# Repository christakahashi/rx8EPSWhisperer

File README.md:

# WARNING
Operating a modified production car can be dangerous or life threatening.  Don't do it.  This project is only for testing your powersteering components in either an otherwise inoperable car or under SLOW SAFE conditions and NEVER on the road or in public. 

# rx8EPSWhisperer
This is a hack to recover the power steering on an RX8 power steering rack thats not longer connected to the ECU.

It reads a potentiometer connected to ADC7 to determine the power steering assist level.

# Hardware
The hardware was designed to be multipurpose as either a CAN sensor interface or to enable the EPS on an RX8.  All components were choosen to be AEC-Q100/AEC-Q200 qualified or have variants that are qualified.  It shoudn't matter for bench test use, but if that matters to you then make sure to buy the right variants.

# Hookup
Connect 12v, ground, CAN+, CAN-, to their respective connections.  If you don't have external termination please close the termination jumper on the PCB.  
To wire it you can either cut the wires on your connector short and run them directly into the PCB making it directly hang off the EPS computer, or you can run longer wires from the 4 pin connector.  Either way 12v and ground need to be connected to the cars accessory power.  

# NOTES
- This isn't a product if anything here doesn't make sense or makes you nervous don't use this hardware/software.
- The can library came modified from atmel, now microchip.  The license referred to in the source for that library can no longer be found, but if its like similar libraries from atmel its free to use as long as its only used on atmel chips.  The licene text file included with this repository only applies to the non-library files.  If you represent atmel/microchip and have clarification or want me to remove the library please contact me.

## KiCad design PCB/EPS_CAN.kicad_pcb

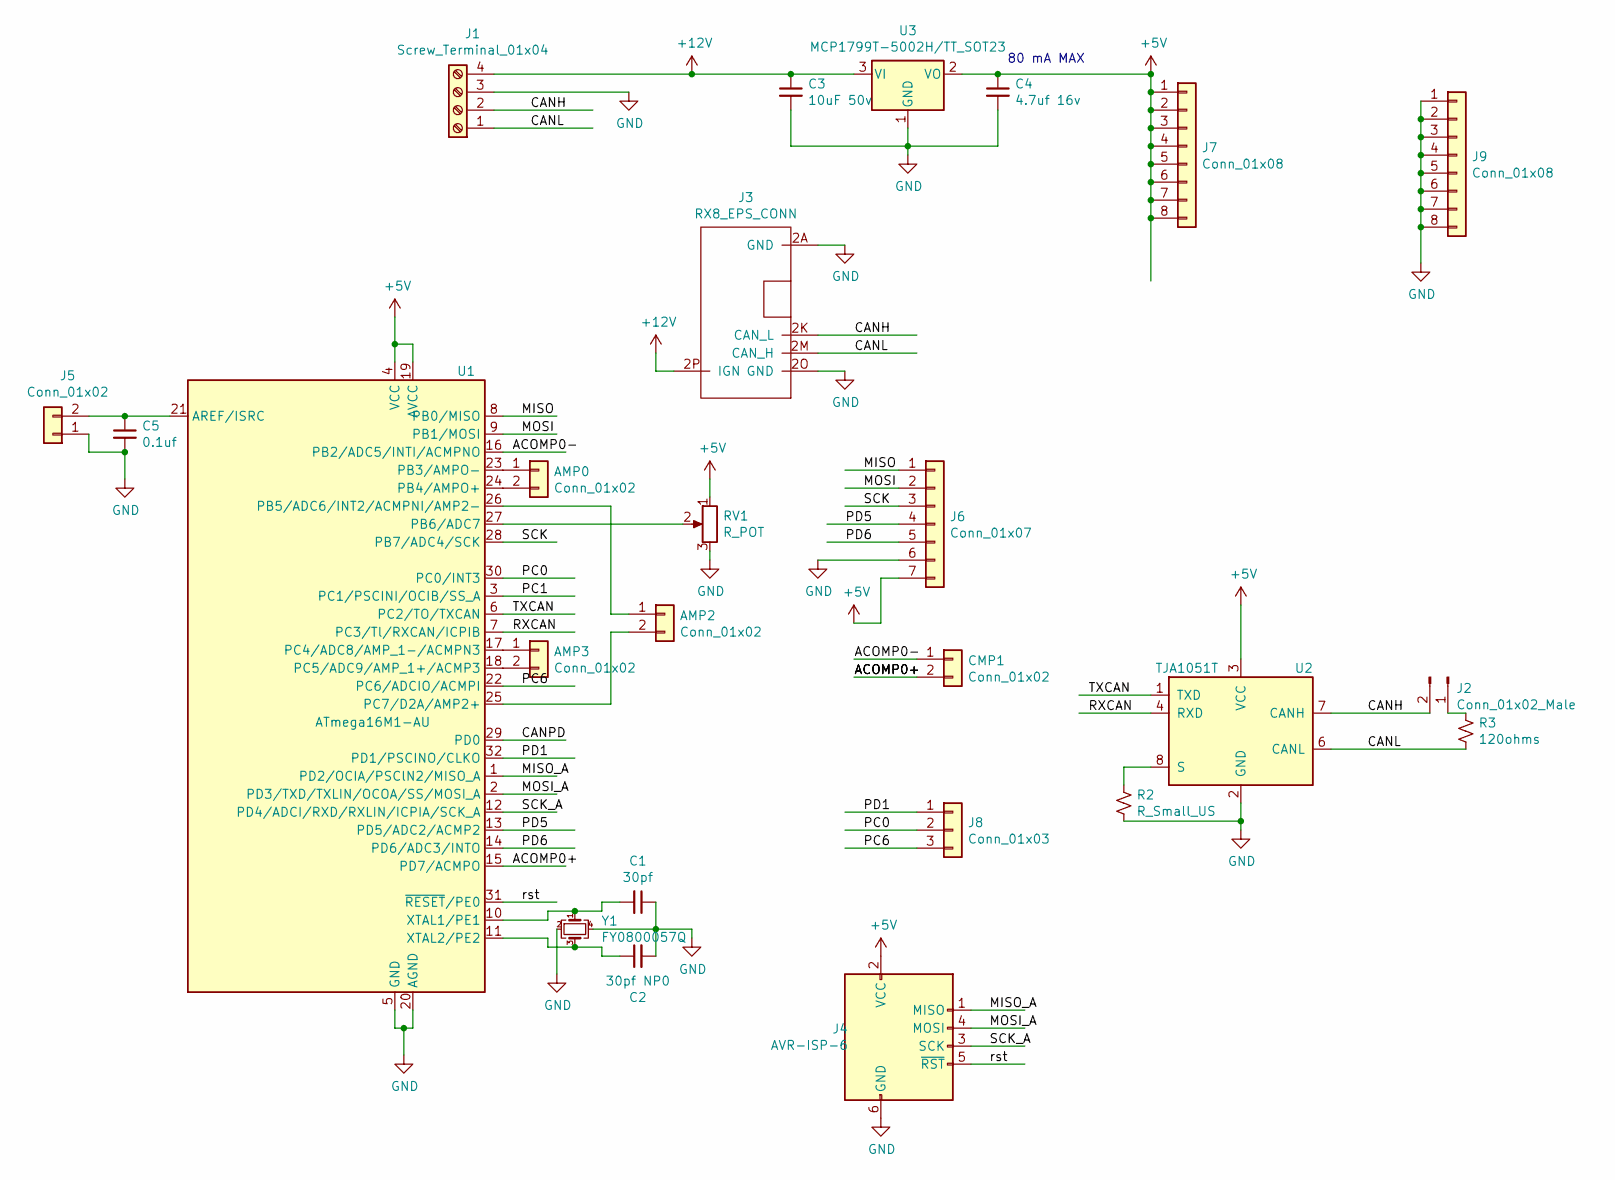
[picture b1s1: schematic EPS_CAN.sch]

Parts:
AMP0, AMP2, AMP3: Conn_01x02; PinHeader_1x02_P2.54mm_SPECIALSILK
C1: 30pf; C_0603_1608Metric
C2: 30pf NP0; C_0603_1608Metric
C3: 10uF 50v; C_1210_3225Metric
C4: 4.7uf 16v; C_0805_2012Metric
C5: 0.1uf; C_0805_2012Metric
CMP1: Conn_01x02; PinHeader_1x02_P2.54mm_SPECIALSILK
J1: Screw_Terminal_01x04; PhoenixContact_MSTBVA_2,5_4-G-5,08_1x04_P5.08mm_Vertical
J2: Conn_01x02_Male; PinHeader_1x02_P2.54mm_Vertical
J3: RX8_EPS_CONN; RX8_EPS_F
J4: AVR-ISP-6; PinHeader_2x03_P2.54mm_Vertical_SMD
J5: Conn_01x02; PinHeader_1x02_P2.54mm_Vertical
J6: Conn_01x07; PinHeader_1x07_P2.54mm_Vertical
J7, J9: Conn_01x08; PinHeader_1x08_P2.54mm_Vertical
J8: Conn_01x03; PinHeader_1x03_P2.54mm_Vertical
R2: R_Small_US; R_0805_2012Metric
R3: 120ohms; R_0805_2012Metric
RV1: R_POT; Potentiometer_Bourns_3314J_Vertical
U1: ATmega16M1-AU; TQFP-32_7x7mm_P0.8mm
U2: TJA1051T; SOIC-8_3.9x4.9mm_P1.27mm
U3: MCP1799T-5002H/TT_SOT23; SOT-23
Y1: FY0800057Q; Crystal_SMD_5032-4Pin_5.0x3.2mm

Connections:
+5V: C4.1, J4.2 (VCC), J6.7, J7.1, J7.2, J7.3, J7.4, J7.5, J7.6, J7.7, J7.8, RV1.1, U1.4 (VCC), U1.19 (AVCC), U2.3 (VCC), U3.2 (VO)
+12V: C3.1, J1.4, J3.2P (IGN), U3.3 (VI)
/ACOMP0+: CMP1.2, U1.15 (PD7/ACMPO)
/ACOMP0-: CMP1.1, U1.16 (PB2/ADC5/INTI/ACMPNO)
/CANH: J1.2, J2.2, J3.2K (CAN_L), U2.7 (CANH)
/CANL: J1.1, J3.2M (CAN_H), R3.2, U2.6 (CANL)
/CANPD: U1.29 (PD0)
/MISO: J6.1, U1.8 (PB0/MISO)
/MISO_A: J4.1 (MISO), U1.1 (PD2/OCIA/PSClN2/MISO_A)
/MOSI: J6.2, U1.9 (PB1/MOSI)
/MOSI_A: J4.4 (MOSI), U1.2 (PD3/TXD/TXLIN/OCOA/SS/MOSI_A)
/PC0: J8.2, U1.30 (PC0/INT3)
/PC1: U1.3 (PC1/PSCINI/OCIB/SS_A)
/PC6: J8.3, U1.22 (PC6/ADCIO/ACMPI)
/PD1: J8.1, U1.32 (PD1/PSCINO/CLKO)
/PD5: J6.4, U1.13 (PD5/ADC2/ACMP2)
/PD6: J6.5, U1.14 (PD6/ADC3/INTO)
/RXCAN: U1.7 (PC3/Tl/RXCAN/ICPIB), U2.4 (RXD)
/SCK: J6.3, U1.28 (PB7/ADC4/SCK)
/SCK_A: J4.3 (SCK), U1.12 (PD4/ADCI/RXD/RXLIN/ICPIA/SCK_A)
/TXCAN: U1.6 (PC2/TO/TXCAN), U2.1 (TXD)
/rst: J4.5 (~RST), U1.31 (~RESET~/PE0)
GND: C1.1, C2.2, C3.2, C4.2, C5.2, J1.3, J3.2A (GND), J3.2O (GND), J4.6 (GND), J5.1, J6.6, J9.1, J9.2, J9.3, J9.4, J9.5, J9.6, J9.7, J9.8, R2.1, RV1.3, U1.5 (GND), U1.20 (AGND), U2.2 (GND), U3.1 (GND), Y1.2, Y1.4
unnamed: AMP0.1, U1.23 (PB3/AMPO-)
unnamed: AMP0.2, U1.24 (PB4/AMPO+)
unnamed: AMP2.1, U1.26 (PB5/ADC6/INT2/ACMPNI/AMP2-)
unnamed: AMP2.2, U1.25 (PC7/D2A/AMP2+)
unnamed: AMP3.1, U1.17 (PC4/ADC8/AMP_1-/ACMPN3)
unnamed: AMP3.2, U1.18 (PC5/ADC9/AMP_1+/ACMP3)
unnamed: C1.2, U1.10 (XTAL1/PE1), Y1.1
unnamed: C2.1, U1.11 (XTAL2/PE2), Y1.3
unnamed: C5.1, J5.2, U1.21 (AREF/ISRC)
unnamed: J2.1, R3.1
unnamed: R2.2, U2.8 (S)
unnamed: RV1.2, U1.27 (PB6/ADC7)

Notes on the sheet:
80 mA MAX

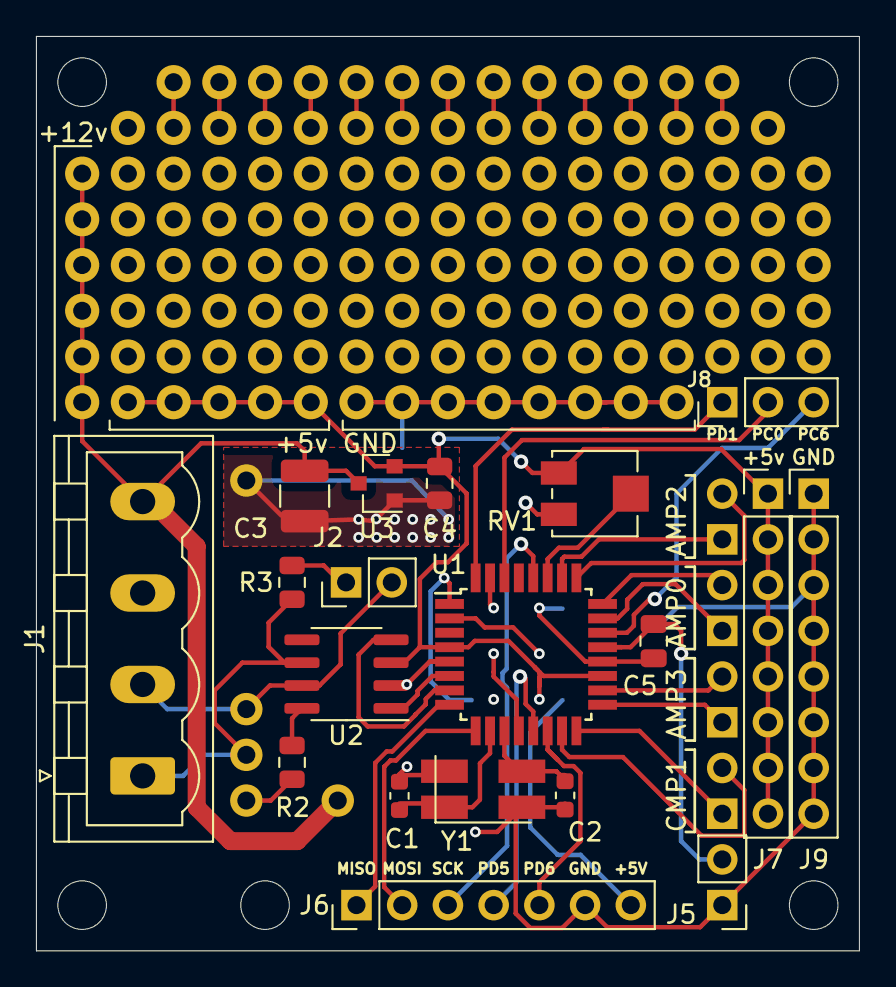
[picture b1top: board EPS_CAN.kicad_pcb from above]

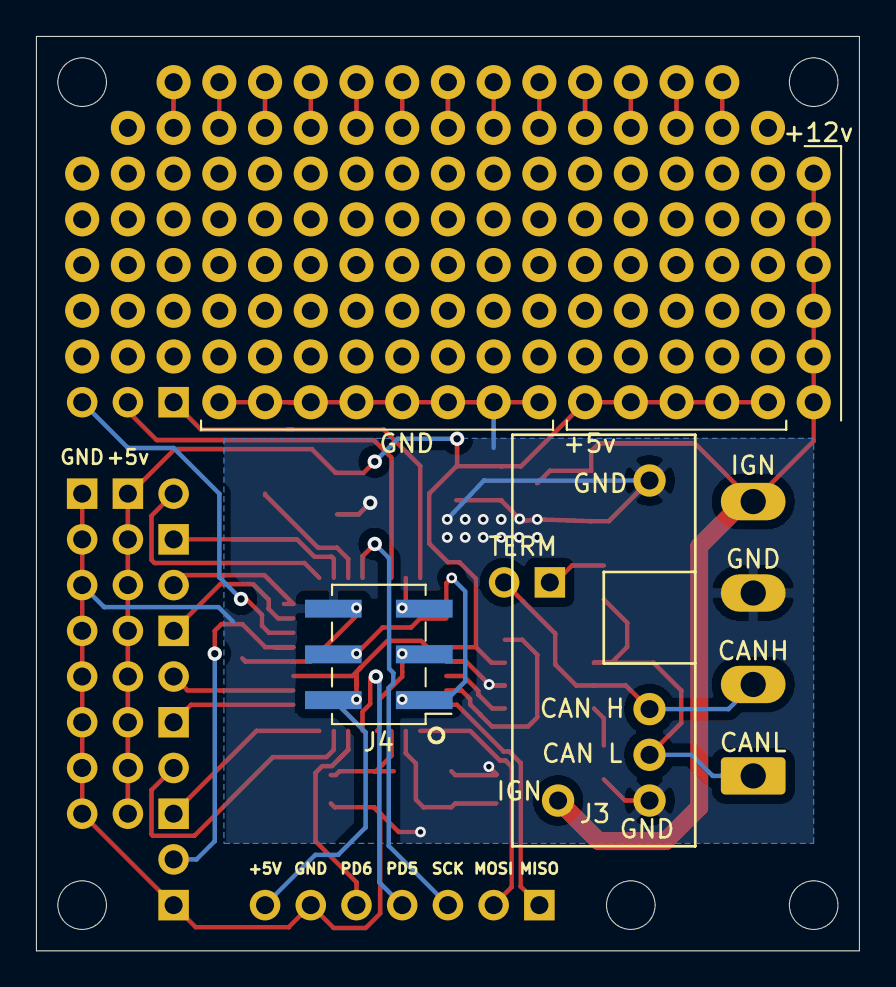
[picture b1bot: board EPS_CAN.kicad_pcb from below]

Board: 2 copper layers, 45.7 x 50.8 mm, 25 parts (2 on the bottom side), 33 nets.

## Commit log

2020-12-20 working could use some optimizations
2021-04-29 fixed the only sending 6 msg thing. and added POT to adjust 'speed' from 0-161kph aka 0-100mph
2021-10-16 new adc channel
2021-10-16 fixed mixed spaces and tabs...
2021-10-16 Create LICENSE
2021-10-16 added PCB
